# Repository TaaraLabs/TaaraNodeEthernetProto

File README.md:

TaaraNode Ethernet Proto
========================

Arduino/JeeNode compatible microcontroller board with on-board Ethernet, RFM12b radio and prototyping area

[WebSite](https://taaralabs.eu/ep1)

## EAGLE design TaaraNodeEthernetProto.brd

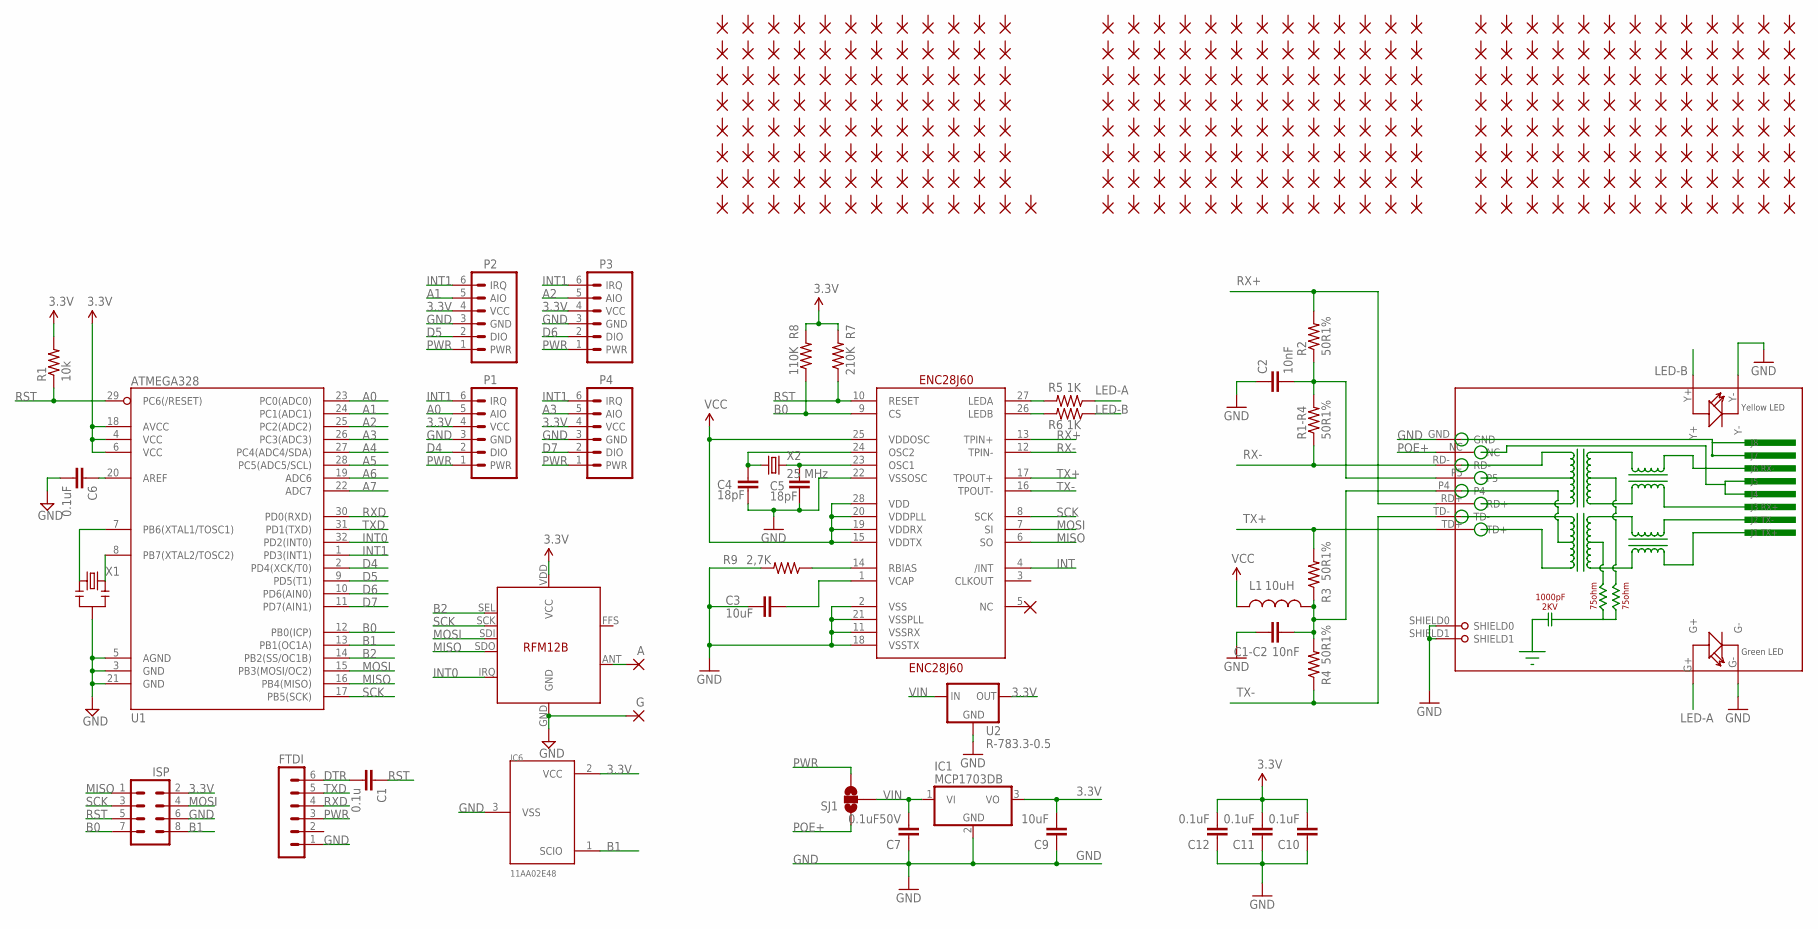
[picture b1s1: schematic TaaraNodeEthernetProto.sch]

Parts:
A: 1,6/0,8
C1: 0.1u; 0603-CAP
C1-C2, C2: 10nF; 0603-CAP
C3, C9: 10uF; 0603-CAP
C4, C5: 18pF; 0603-CAP
C6, C10, C11, C12: 0.1uF; 0603-CAP
C7: 0.1uF50V; 0603-CAP
ENC28J60: ENC28J60; SSOP28DB
FTDI: MA06-1
G: 1,6/0,8
IC1: MCP1703DB; SOT223
IC6: 11AA02E48; SOT23
L1: 10uH; 0805
P1, P2, P3, P4: JEEPORT-FEMALE; 1X06_FEMALE_LOCK.010
PAD1, PAD2, PAD3, PAD4, PAD5, PAD6, PAD7, PAD8, PAD9, PAD10, PAD11, PAD12, PAD13, PAD14, PAD15, PAD16, PAD17, PAD18, PAD19, PAD20, PAD21, PAD22, PAD23, PAD24, PAD25, PAD26, PAD27, PAD28, PAD29, PAD30, PAD31, PAD32, PAD33, PAD34, PAD35, PAD36, PAD37, PAD38, PAD39, PAD40, PAD41, PAD42, PAD43, PAD44, PAD45, PAD46, PAD47, PAD48, PAD49, PAD50, PAD51, PAD52, PAD53, PAD54, PAD55, PAD56, PAD57, PAD58, PAD59, PAD60, PAD61, PAD62, PAD63, PAD64, PAD65, PAD66, PAD67, PAD68, PAD69, PAD70, PAD71, PAD72, PAD73, PAD74, PAD75, PAD76, PAD77, PAD78, PAD79, PAD80, PAD81, PAD82, PAD83, PAD84, PAD85, PAD86, PAD87, PAD88, PAD89, PAD90, PAD91, PAD92, PAD93, PAD94, PAD95, PAD96, PAD97, PAD98, PAD99, PAD100, PAD101, PAD102, PAD103, PAD104, PAD105, PAD106, PAD107, PAD108, PAD109, PAD110, PAD111, PAD112, PAD113, PAD114, PAD115, PAD116, PAD117, PAD118, PAD119, PAD120, PAD121, PAD122, PAD123, PAD124, PAD125, PAD126, PAD127, PAD128, PAD129, PAD130, PAD131, PAD132, PAD133, PAD134, PAD135, PAD136, PAD137, PAD138, PAD139, PAD140, PAD141, PAD142, PAD143, PAD144, PAD145, PAD146, PAD147, PAD148, PAD149, PAD150, PAD151, PAD152, PAD153, PAD154, PAD155, PAD156, PAD157, PAD158, PAD159, PAD160, PAD161, PAD162, PAD163, PAD164, PAD165, PAD166, PAD167, PAD168, PAD169, PAD170, PAD171, PAD172, PAD173, PAD174, PAD175, PAD176, PAD177, PAD178, PAD179, PAD180, PAD181, PAD182, PAD183, PAD184, PAD185, PAD186, PAD187, PAD188, PAD189, PAD190, PAD191, PAD192, PAD193, PAD194, PAD195, PAD196, PAD197, PAD198, PAD199, PAD200, PAD201, PAD202, PAD203, PAD204, PAD205, PAD206, PAD207, PAD208, PAD209, PAD210, PAD211, PAD212, PAD213, PAD214, PAD215, PAD216, PAD217, PAD218, PAD219, PAD220, PAD221, PAD222, PAD223, PAD224, PAD225, PAD226, PAD227, PAD228, PAD229, PAD230, PAD231, PAD232, PAD233, PAD234, PAD235, PAD236, PAD237, PAD238, PAD239, PAD240, PAD241, PAD242, PAD243, PAD244, PAD245, PAD246, PAD247, PAD248, PAD249, PAD250, PAD251, PAD252, PAD253, PAD254, PAD255, PAD256, PAD257, PAD258, PAD259, PAD260, PAD261, PAD262, PAD263, PAD264, PAD265, PAD266, PAD267, PAD268, PAD269, PAD270, PAD271, PAD272, PAD273, PAD274, PAD275, PAD276, PAD277, PAD278, PAD279, PAD280, PAD281, PAD282, PAD283, PAD284, PAD285, PAD286, PAD287, PAD288, PAD289, PAD290, PAD291, PAD292, PAD293, PAD294, PAD295, PAD296, PAD297, PAD298, PAD299, PAD300, PAD301, PAD302, PAD303, PAD304, PAD305: 1,6/0,8
R1: 10k; 0603-RES
R1-R4, R2, R3, R4: 50R1%; 0603-RES
R5, R6: 1K; 0603-RES
R7: 210K; 0603-RES
R8: 110K; 0603-RES
R9: 2,7K; 0603-RES
RJ1: HLJ-6115ANL; HR911105A
SJ1: SOLDERJUMPER_2WAYT; SJ_2
SV7: ISP; MA04-2
U1: ATMEGA328; TQFP32-08
U2: R-783.3-0.5; R-78XX
U$1: RFM12B
X1: RESONATORSMD; RESONATOR-SMD
X2: 25 MHz; CRYSTAL-SMD-3.2X2.5

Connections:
3.3V: C9.2, C10.2, C11.2, C12.2, ENC28J60.15 (VDDTX), ENC28J60.19 (VDDRX), ENC28J60.20 (VDDPLL), ENC28J60.25 (VDDOSC), ENC28J60.28 (VDD), IC1.3 (VO), IC6.2 (VCC), L1.1, P1.4 (VCC), P2.4 (VCC), P3.4 (VCC), P4.4 (VCC), R1.2, R7.2, R8.2, SV7.2, U1.4 (VCC), U1.6 (VCC), U1.18 (AVCC), U2.OUT, U$1.VDD (VCC)
A0: P1.5 (AIO), U1.23 (PC0(ADC0))
A1: P2.5 (AIO), U1.24 (PC1(ADC1))
A2: P3.5 (AIO), U1.25 (PC2(ADC2))
A3: P4.5 (AIO), U1.26 (PC3(ADC3))
A4: U1.27 (PC4(ADC4/SDA))
A5: U1.28 (PC5(ADC5/SCL))
A6: U1.19 (ADC6)
A7: U1.22 (ADC7)
B0: ENC28J60.9 (CS), R8.1, SV7.7, U1.12 (PB0(ICP))
B1: IC6.1 (SCIO), SV7.8, U1.13 (PB1(OC1A))
B2: U1.14 (PB2(SS/OC1B)), U$1.SEL
D4: P1.2 (DIO), U1.2 (PD4(XCK/T0))
D5: P2.2 (DIO), U1.9 (PD5(T1))
D6: P3.2 (DIO), U1.10 (PD6(AIN0))
D7: P4.2 (DIO), U1.11 (PD7(AIN1))
DTR: C1.2, FTDI.6
GND: C1-C2.1, C2.1, C3.1, C4.1, C5.1, C6.2, C7.1, C9.1, C10.1, C11.1, C12.1, ENC28J60.2 (VSS), ENC28J60.11 (VSSRX), ENC28J60.18 (VSSTX), ENC28J60.21 (VSSPLL), ENC28J60.22 (VSSOSC), FTDI.1, G.1, IC1.2 (GND), IC6.3 (VSS), P1.3 (GND), P2.3 (GND), P3.3 (GND), P4.3 (GND), R9.2, RJ1.G-, RJ1.GND, RJ1.SHIELD0, RJ1.SHIELD1, RJ1.Y-, SV7.6, U1.3 (GND), U1.5 (AGND), U1.21 (GND), U2.GND, U$1.GND, X1.2
INT: ENC28J60.4 (/INT)
INT0: U1.32 (PD2(INT0)), U$1.IRQ
INT1: P1.6 (IRQ), P2.6 (IRQ), P3.6 (IRQ), P4.6 (IRQ), U1.1 (PD3(INT1))
LED-A: R5.1, RJ1.G+
LED-B: R6.1, RJ1.Y+
MISO: ENC28J60.6 (SO), SV7.1, U1.16 (PB4(MISO)), U$1.SDO
MOSI: ENC28J60.7 (SI), SV7.4, U1.15 (PB3(MOSI/OC2)), U$1.SDI
unnamed: U1.7 (PB6(XTAL1/TOSC1)), X1.1
unnamed: C6.1, U1.20 (AREF)
unnamed: ENC28J60.27 (LEDA), R5.2
unnamed: ENC28J60.26 (LEDB), R6.2
unnamed: ENC28J60.14 (RBIAS), R9.1
unnamed: C3.2, ENC28J60.1 (VCAP)
unnamed: C4.2, ENC28J60.24 (OSC2), X2.1
unnamed: C5.2, ENC28J60.23 (OSC1), X2.3 (2)
unnamed: A.1, U$1.ANT
unnamed: U1.8 (PB7(XTAL2/TOSC2)), X1.3
POE+: RJ1.NC, SJ1.1
PWR: FTDI.3, P1.1 (PWR), P2.1 (PWR), P3.1 (PWR), P4.1 (PWR), SJ1.3
RCT: C2.2, R1-R4.2, R2.1, RJ1.P5
RST: C1.1, ENC28J60.10 (RESET), R1.1, R7.1, SV7.5, U1.29 (PC6(/RESET))
RX+: ENC28J60.13 (TPIN+), R2.2, RJ1.RD+
RX-: ENC28J60.12 (TPIN-), R1-R4.1, RJ1.RD-
RXD: FTDI.4, U1.30 (PD0(RXD))
SCK: ENC28J60.8 (SCK), SV7.3, U1.17 (PB5(SCK)), U$1.SCK
TCT: C1-C2.2, L1.2, R3.1, R4.2, RJ1.P4
TX+: ENC28J60.17 (TPOUT+), R3.2, RJ1.TD+
TX-: ENC28J60.16 (TPOUT-), R4.1, RJ1.TD-
TXD: FTDI.5, U1.31 (PD1(TXD))
VIN: C7.2, IC1.1 (VI), SJ1.2, U2.IN

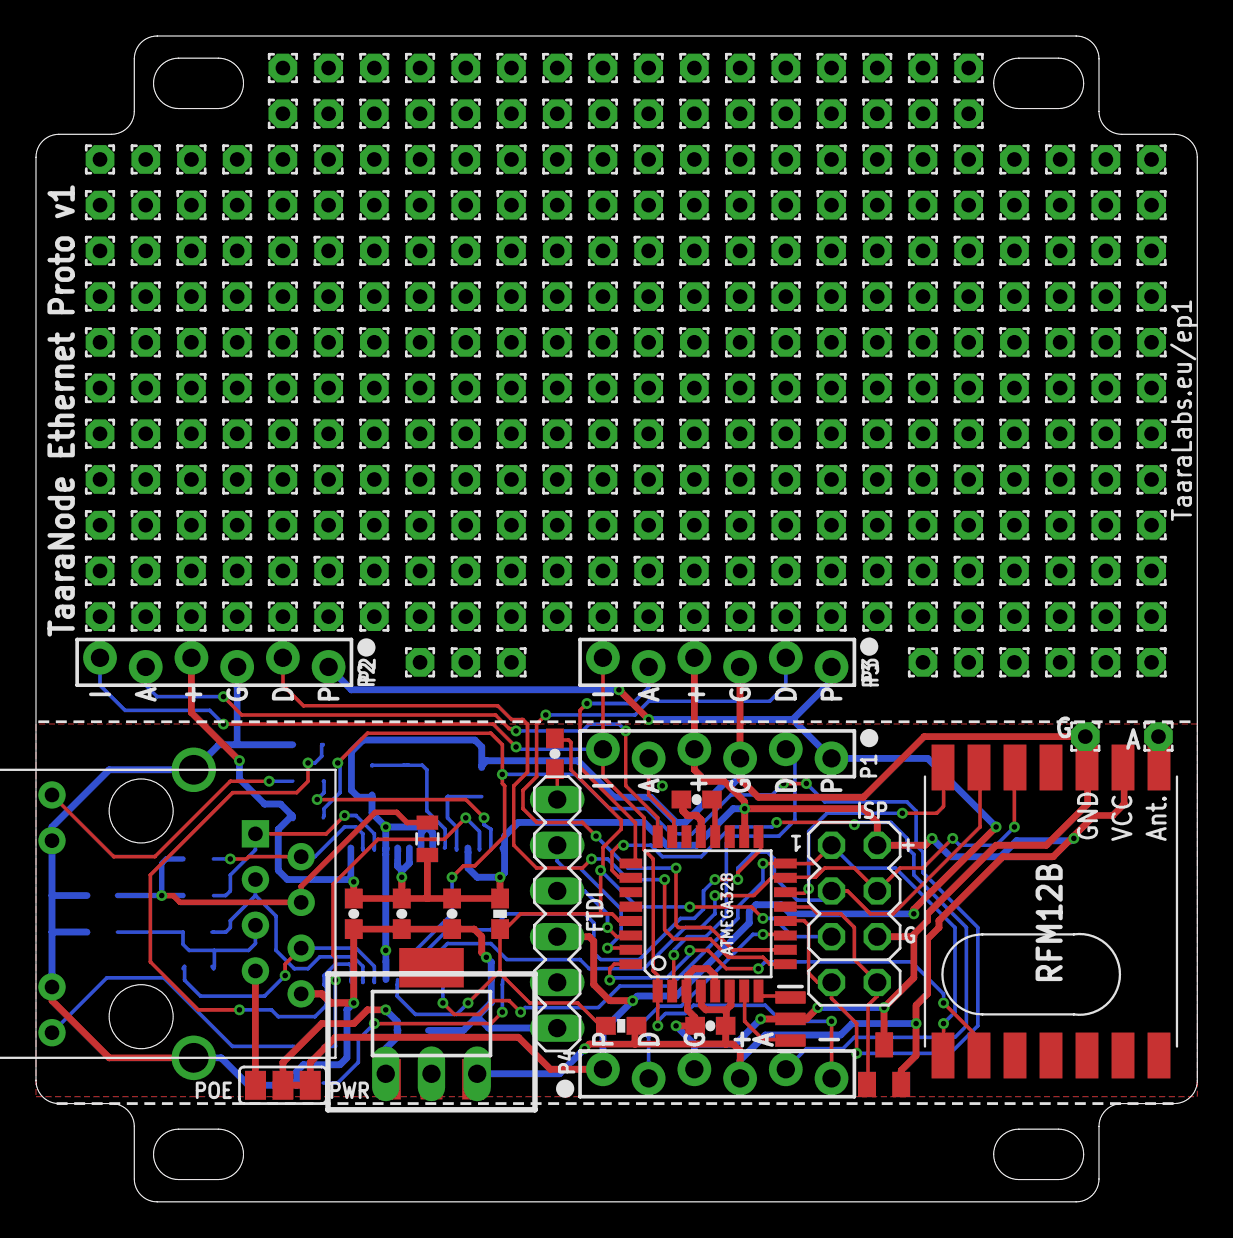
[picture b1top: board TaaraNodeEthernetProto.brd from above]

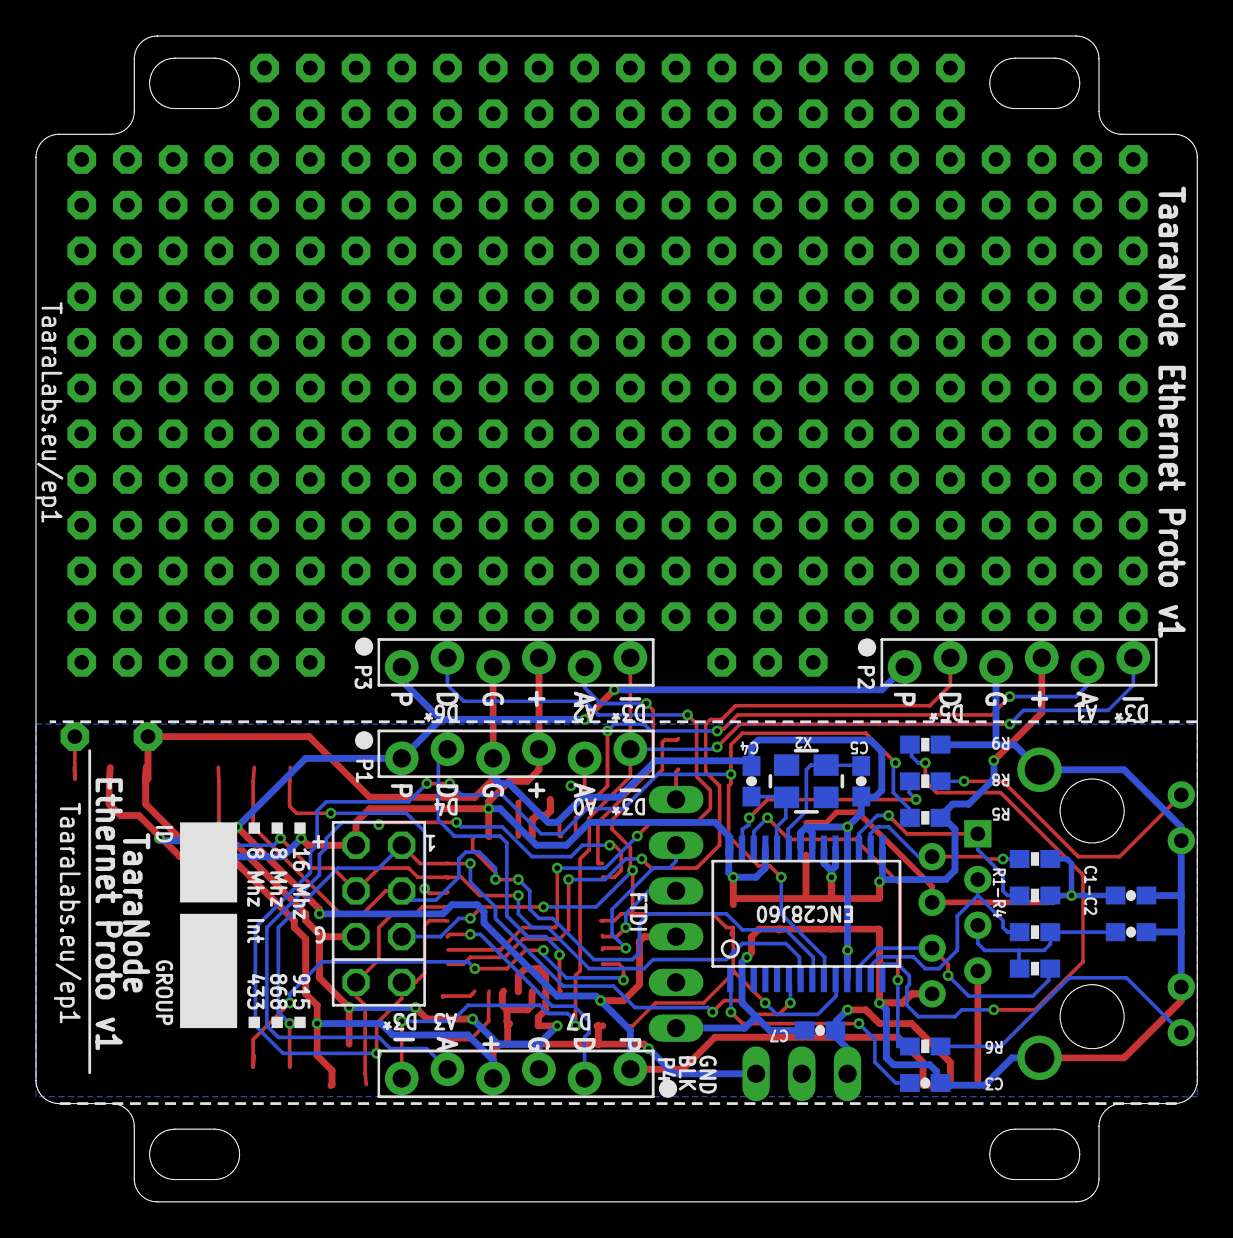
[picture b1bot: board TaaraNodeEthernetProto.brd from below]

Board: 2 copper layers, 64.5 x 64.8 mm, 347 parts (16 on the bottom side), 43 nets.

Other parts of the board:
U$2: NODEPARAMS

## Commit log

2015-01-22 :octocat: Added .gitattributes & .gitignore files
2015-01-22 TaaraNodeEthernetProto
